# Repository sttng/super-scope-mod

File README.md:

# super-scope-mod
Tracking, BT communication code, and 3D printer files to make SNES Super Scope work on LCD TVs

## Description
This is the companion code for *element14 Presents* episode 469: "Nintendo Super Scope Mod For Modern Televisions".

element14 Community page: https://www.element14.com/community/docs/DOC-95663

# Bill of Material

| Product Name | Manufacturer | Quantity |
| ------------ | ------------ | -------- |
| RPI4-MODBP-2GB - Single Board Computer, Raspberry Pi 4 Model B, BCM2711 SoC, 2GB DDR4 RAM, USB 3.0, PoE Enabled   | RASPBERRY-PI | 1 |
| Development Board, Arduino Uno, ATmega328P MCU, 14 3.3V I/O, 6 Analogue Inputs, 6 PWM Outputs                     | ARDUINO      | 1 |
| RPI NOIR CAMERA BOARD - Daughter Board, Raspberry Pi NoIR Camera Board, Version 2, Sony IMX219 8-Megapixel Sensor | RASPBERRY-PI | 1 |
| MP001243 - AXIAL FAN, RASPBERRY PI 4 POWER HAT CASE | MULTICOMP PRO | 1 |
| Infrared Emitter, High Speed, 850 nm, 3 °, T-1 3/4 (5mm), 10 mW/Sr, 10 ns, 10 ns | VISHAY | 4 |
| LM1881N Video Sync Separator chip | TI | 1 |
| MC14021BCP 8Bit Shift Register chip | Motorola | 1 |
| 680k Ohm resistor | | 1 |
| 0.1 µF ceramic capacitors | | 2 |

# Additional Parts

| Product Name |
| ------------ |
| 3 x 3" Infrared (87C) Polyester Filter |
| Moldable glue, black color |
| HC-06 Bluetooth 2.0 Module |
| 30cm Micro HDMI Male to Micro HDMI Female Extension Cable |
| 30cm USB Type C Extension Cable Male to Female |
| 50cm flat ribbon camera cable for Raspberry Pi cameras |

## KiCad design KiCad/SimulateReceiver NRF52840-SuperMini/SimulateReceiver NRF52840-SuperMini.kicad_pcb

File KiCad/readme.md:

# Arduino Nano Shield KiCad 9 files

An Arduino Nano shield version of the Super Scope Mod. It is supposed to go below an Arduino Nano. 
The orientation is marked with the USB (top) marker. This is where the Arduino Nanos USB port is supposed to be (on top), with the shield below.

## Device

## BoM

| Designator  | Footprint                                          | Quantity | Description   |
|-------------|----------------------------------------------------|----------|---------------|
| J1, J2      | PinSocket_1x15_P2.54mm_Vertical                    | 2        |               |
| J4          | Molex_PicoBlade_53048-0610_1x06_P1.25mm_Horizontal | 1        |               |
| C1,C2,C3,C3 | C_0805_2012Metric_Pad1.18x1.45mm_HandSolder        | 4        | 0.1µF         |
| R1          | R_0805_2012Metric_Pad1.20x1.40mm_HandSolder        | 1        | 680k          |
| IC1         | DIP-16_W7.62mm                                     | 1        | MC14021BCP    |
| U1          | JEITA_SOIC-8_3.9x4.9mm_P1.27mm                     | 1        | LM1881M       |

# ESP32-S3 Super Mini Shield KiCad 9 files

An ESP32-S3 Super Mini shield version of the Super Scope Mod. It is supposed to go below an ESP32-S3 Super Mini board. 
The orientation is marked with the USB (top) marker. This is where the ESP32-S3 Super Mini USB port is supposed to be (on top), with the shield below.

## Device

## BoM

| Designator  | Footprint                                          | Quantity | Description   |
|-------------|----------------------------------------------------|----------|---------------|
| J1, J2      | PinSocket_1x09_P2.54mm_Vertical                    | 2        |               |
| J3          | JST PH 1x02 P2.00mm Horizontal                     | 1        | to Connect to Coax |
| J4          | Molex_PicoBlade_53048-0610_1x06_P1.25mm_Horizontal | 1        |               |
| C1,C2,C3,C3 | C_0805_2012Metric_Pad1.18x1.45mm_HandSolder        | 4        | 0.1µF         |
| R1          | R_0805_2012Metric_Pad1.20x1.40mm_HandSolder        | 1        | 680k          |
| IC1         | JEITA_SOIC-16_3.9x9.9mm_P1.27mm                    | 1        | CD4021BM96    |
| U1          | JEITA_SOIC-8_3.9x4.9mm_P1.27mm                     | 1        | LM1881M       |

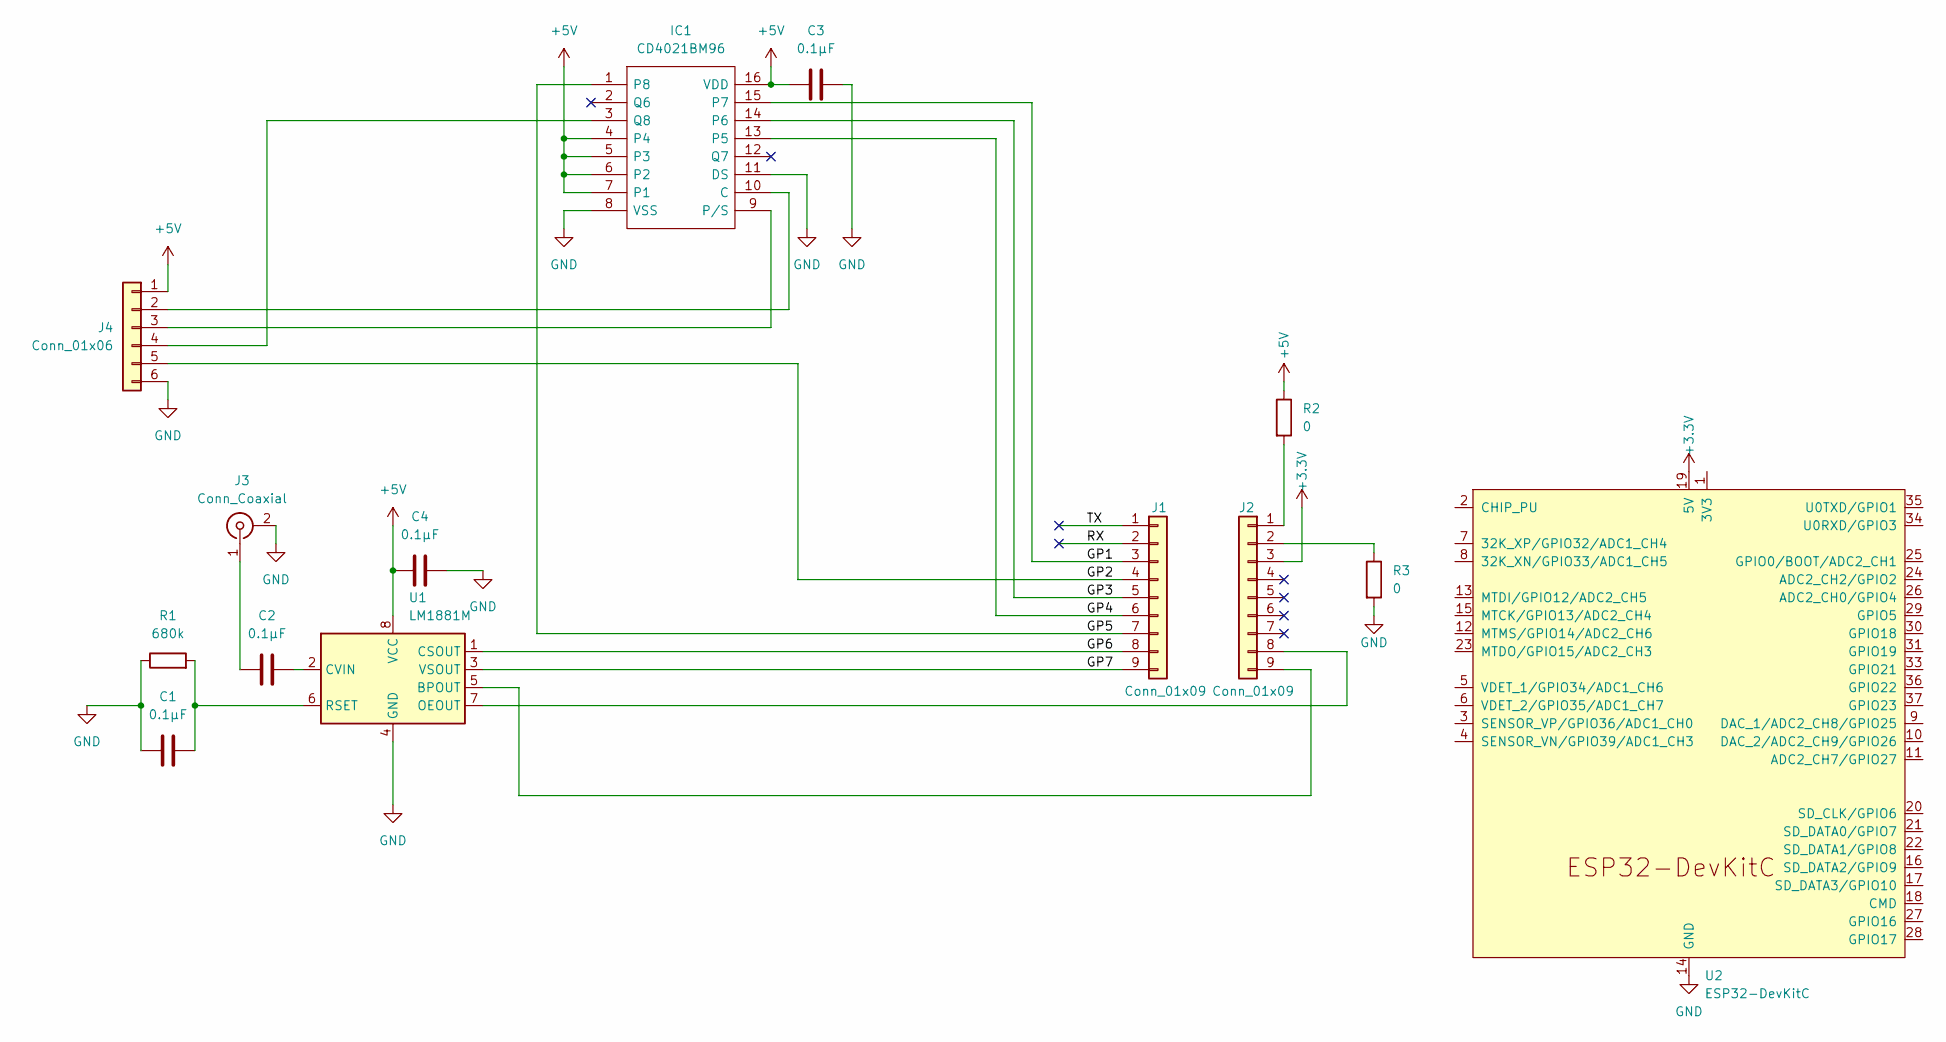
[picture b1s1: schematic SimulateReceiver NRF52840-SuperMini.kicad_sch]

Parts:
C1, C2, C3, C4: 0.1µF; C_0805_2012Metric_Pad1.18x1.45mm_HandSolder
IC1: CD4021BM96; JEITA_SOIC-16_3.9x9.9mm_P1.27mm; Mouser Part Number 863-MC14021BDG
J1, J2: Conn_01x09; PinSocket_1x09_P2.54mm_Vertical
J3: Conn_Coaxial; JST_PH_S2B-PH-K_1x02_P2.00mm_Horizontal
J4: Conn_01x06; Molex_PicoBlade_53048-0610_1x06_P1.25mm_Horizontal
R1: 680k; R_0805_2012Metric_Pad1.20x1.40mm_HandSolder
R2, R3: 0; R_0603_1608Metric_Pad0.98x0.95mm_HandSolder
U1: LM1881M; JEITA_SOIC-8_3.9x4.9mm_P1.27mm
U2: ESP32-DevKitC; ESP32-S3-SuperMini

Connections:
+3.3V: J2.3, U2.19 (5V)
+5V: C3.1, C4.1, IC1.4, IC1.5 (P3), IC1.6 (P2), IC1.7 (P1), IC1.16 (VDD), J4.1, R2.1, U1.8 (VCC)
/GP1: IC1.15 (P7), J1.3
/GP2: J1.4, J4.5
/GP3: IC1.14 (P6), J1.5
/GP4: IC1.13 (P5), J1.6
/GP5: IC1.1 (P8), J1.7
/GP6: J1.8, U1.1 (CSOUT)
/GP7: J1.9, U1.3 (VSOUT)
/RX: J1.2
/TX: J1.1
GND: C1.1, C3.2, C4.2, IC1.8 (VSS), IC1.11 (DS), J3.2 (Ext), J4.6, R1.1, R3.2, U1.4 (GND), U2.14 (GND), U2.32 (GND), U2.38 (GND)
unnamed: IC1.10 (C), J4.2
unnamed: IC1.9 (P/S), J4.3
unnamed: IC1.3 (Q8), J4.4
unnamed: J2.1, R2.2
unnamed: J2.2, R3.1
unnamed: J2.8, U1.7 (OEOUT)
unnamed: J2.9, U1.5 (BPOUT)
unnamed: C2.1, J3.1 (In)
unnamed: C2.2, U1.2 (CVIN)
unnamed: C1.2, R1.2, U1.6 (RSET)

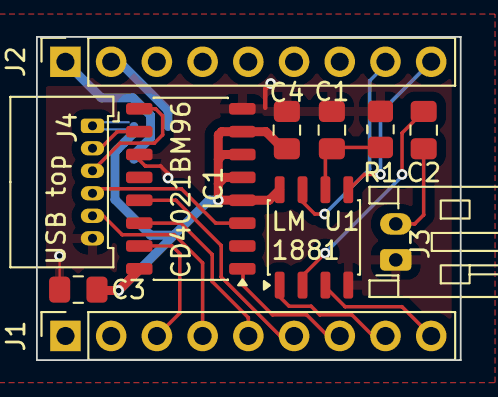
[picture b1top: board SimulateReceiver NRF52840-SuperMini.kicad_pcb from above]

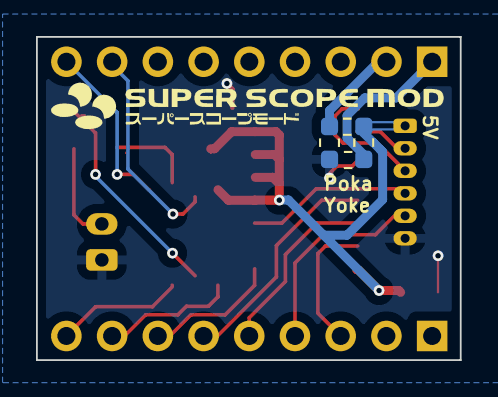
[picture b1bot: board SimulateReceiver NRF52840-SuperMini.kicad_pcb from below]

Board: 4 copper layers, 23.5 x 18.0 mm, 13 parts (2 on the bottom side), 19 nets.

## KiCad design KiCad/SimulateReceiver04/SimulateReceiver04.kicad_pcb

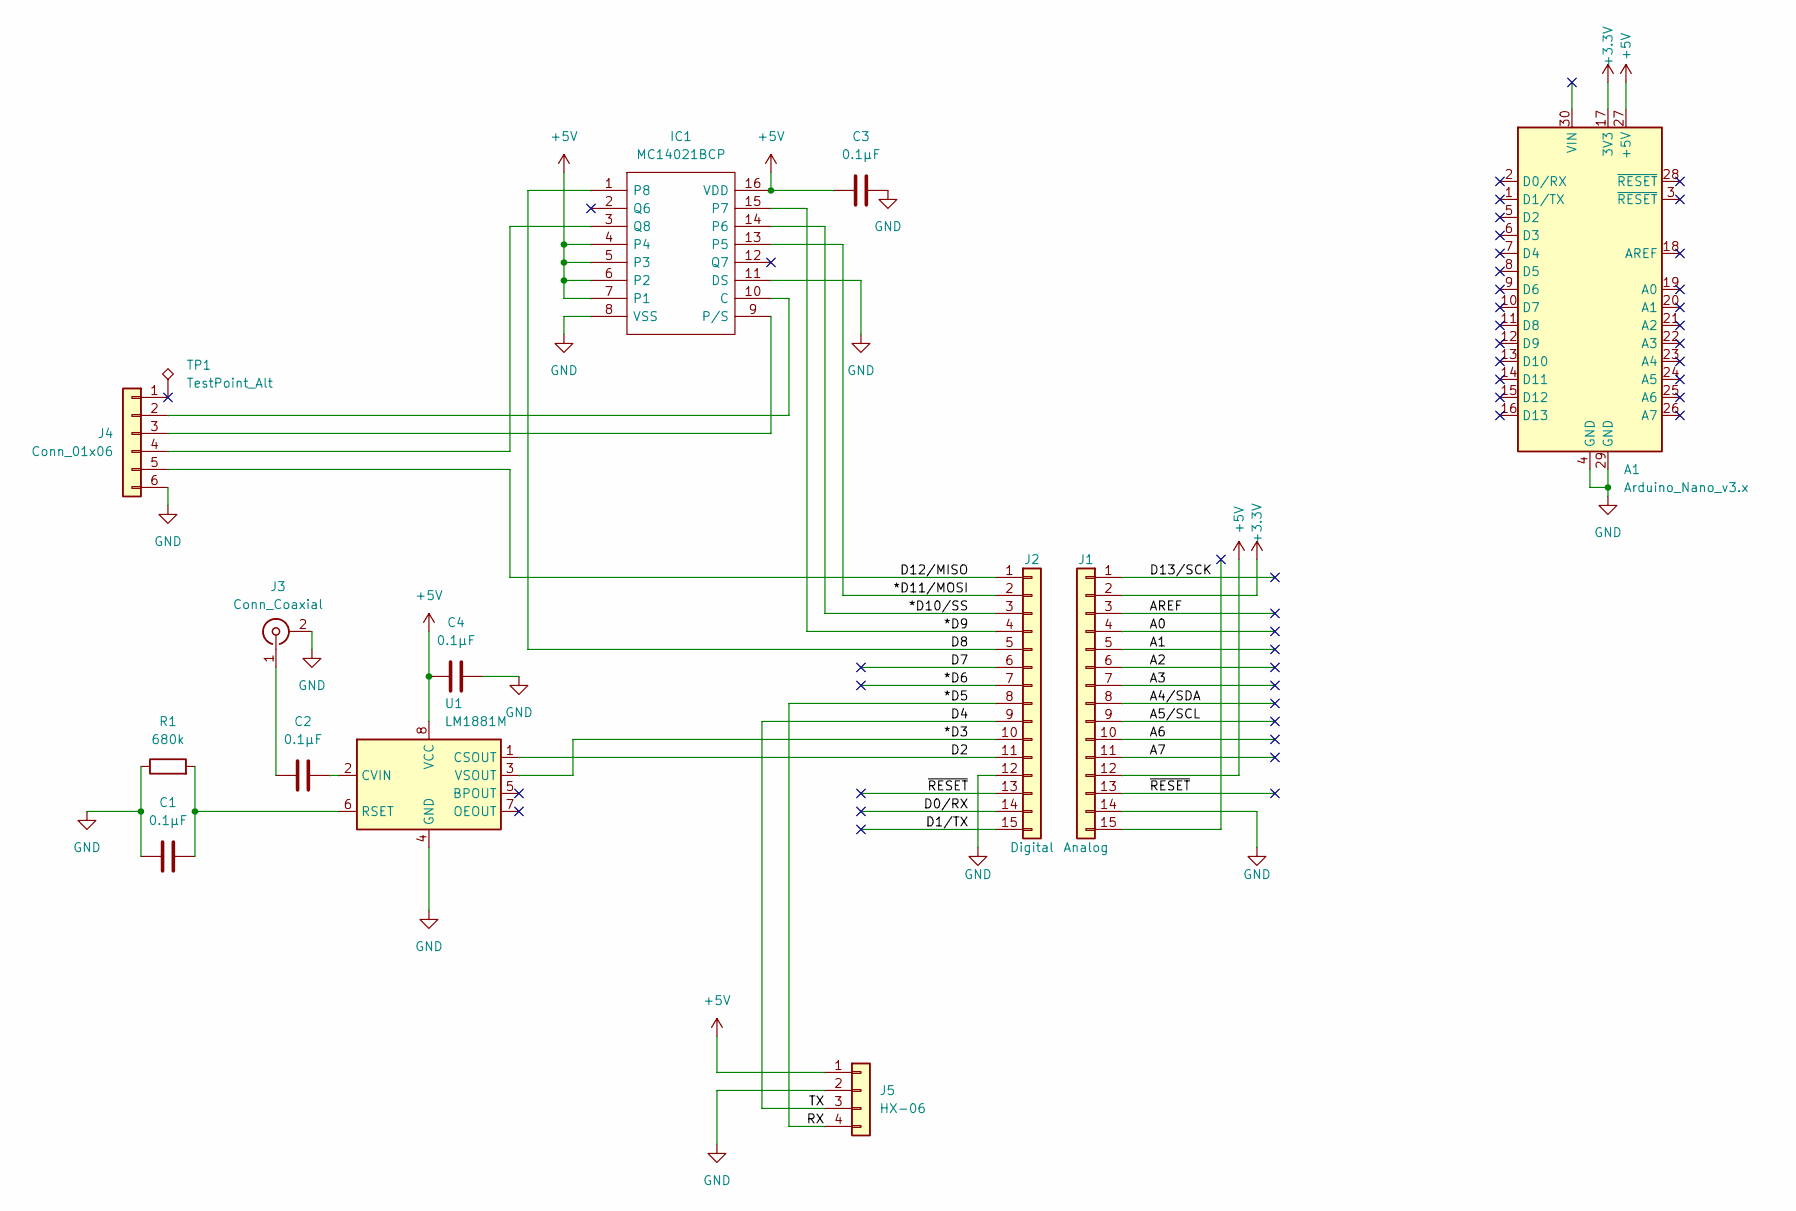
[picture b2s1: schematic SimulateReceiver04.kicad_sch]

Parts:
A1: Arduino_Nano_v3.x; Arduino_Nano
C1, C2, C3, C4: 0.1µF; C_0805_2012Metric_Pad1.18x1.45mm_HandSolder
IC1: MC14021BCP; DIP-16_W7.62mm; Mouser Part Number 863-MC14021BDG
J1: Analog; PinSocket_1x15_P2.54mm_Vertical
J2: Digital; PinSocket_1x15_P2.54mm_Vertical
J3: Conn_Coaxial; PinHeader_1x02_P2.54mm_Vertical
J4: Conn_01x06; Molex_PicoBlade_53048-0610_1x06_P1.25mm_Horizontal
J5: HX-06; PinHeader_1x04_P2.54mm_Vertical
R1: 680k; R_0805_2012Metric_Pad1.20x1.40mm_HandSolder
TP1: TestPoint_Alt; PinHeader_1x01_P1.27mm_Vertical
U1: LM1881M; JEITA_SOIC-8_3.9x4.9mm_P1.27mm

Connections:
+3.3V: A1.17 (3V3), J1.2
+5V: A1.27 (+5V), C3.1, C4.1, IC1.4, IC1.5 (P3), IC1.6 (P2), IC1.7 (P1), IC1.16 (VDD), J1.12, J5.1, U1.8 (VCC)
/*D3: J2.10, U1.3 (VSOUT)
/*D5: J2.8, J5.4
/*D6: J2.7
/*D9: IC1.15 (P7), J2.4
/*D10/SS: IC1.14 (P6), J2.3
/*D11/MOSI: IC1.13 (P5), J2.2
/A0: J1.4
/A1: J1.5
/A2: J1.6
/A3: J1.7
/A4/SDA: J1.8
/A5/SCL: J1.9
/A6: J1.10
/A7: J1.11
/AREF: J1.3
/D0/RX: J2.14
/D1/TX: J2.15
/D2: J2.11, U1.1 (CSOUT)
/D4: J2.9, J5.3
/D7: J2.6
/D8: IC1.1 (P8), J2.5
/D12/MISO: J2.1, J4.5
/D13/SCK: J1.1
/~RESET: J1.13, J2.13
GND: A1.4 (GND), A1.29 (GND), C1.1, C3.2, C4.2, IC1.8 (VSS), IC1.11 (DS), J1.14, J2.12, J3.2 (Ext), J4.6, J5.2, R1.1, U1.4 (GND)
unnamed: IC1.10 (C), J4.2
unnamed: IC1.9 (P/S), J4.3
unnamed: IC1.3 (Q8), J4.4
unnamed: C2.1, J3.1 (In)
unnamed: C2.2, U1.2 (CVIN)
unnamed: C1.2, R1.2, U1.6 (RSET)

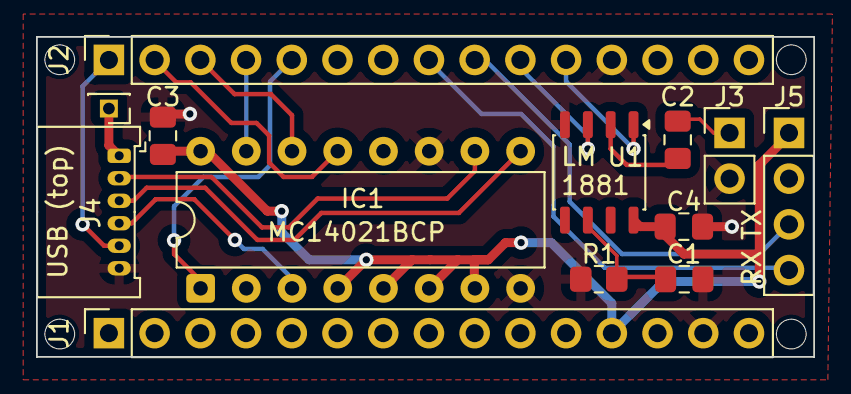
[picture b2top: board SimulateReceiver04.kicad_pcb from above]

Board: 4 copper layers, 43.2 x 17.8 mm, 17 parts (0 on the bottom side), 18 nets.

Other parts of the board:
MH1, MH2, MH3, MH4: MountingHole_65mil
